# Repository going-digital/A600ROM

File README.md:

# A600ROM
Flash ROM Kickstart replacement for the Amiga A600

## This project is in development and currently untested.

This project replaces the Kickstart ROM in the Amiga A600 with a 2M x 16 Flash chip. This allows 4 x 512kB or 2 x 1MB Flash banks.

Initial programming of the first Kickstart must be done with a programmer. But after that, programming can be done in-circuit from the Amiga.

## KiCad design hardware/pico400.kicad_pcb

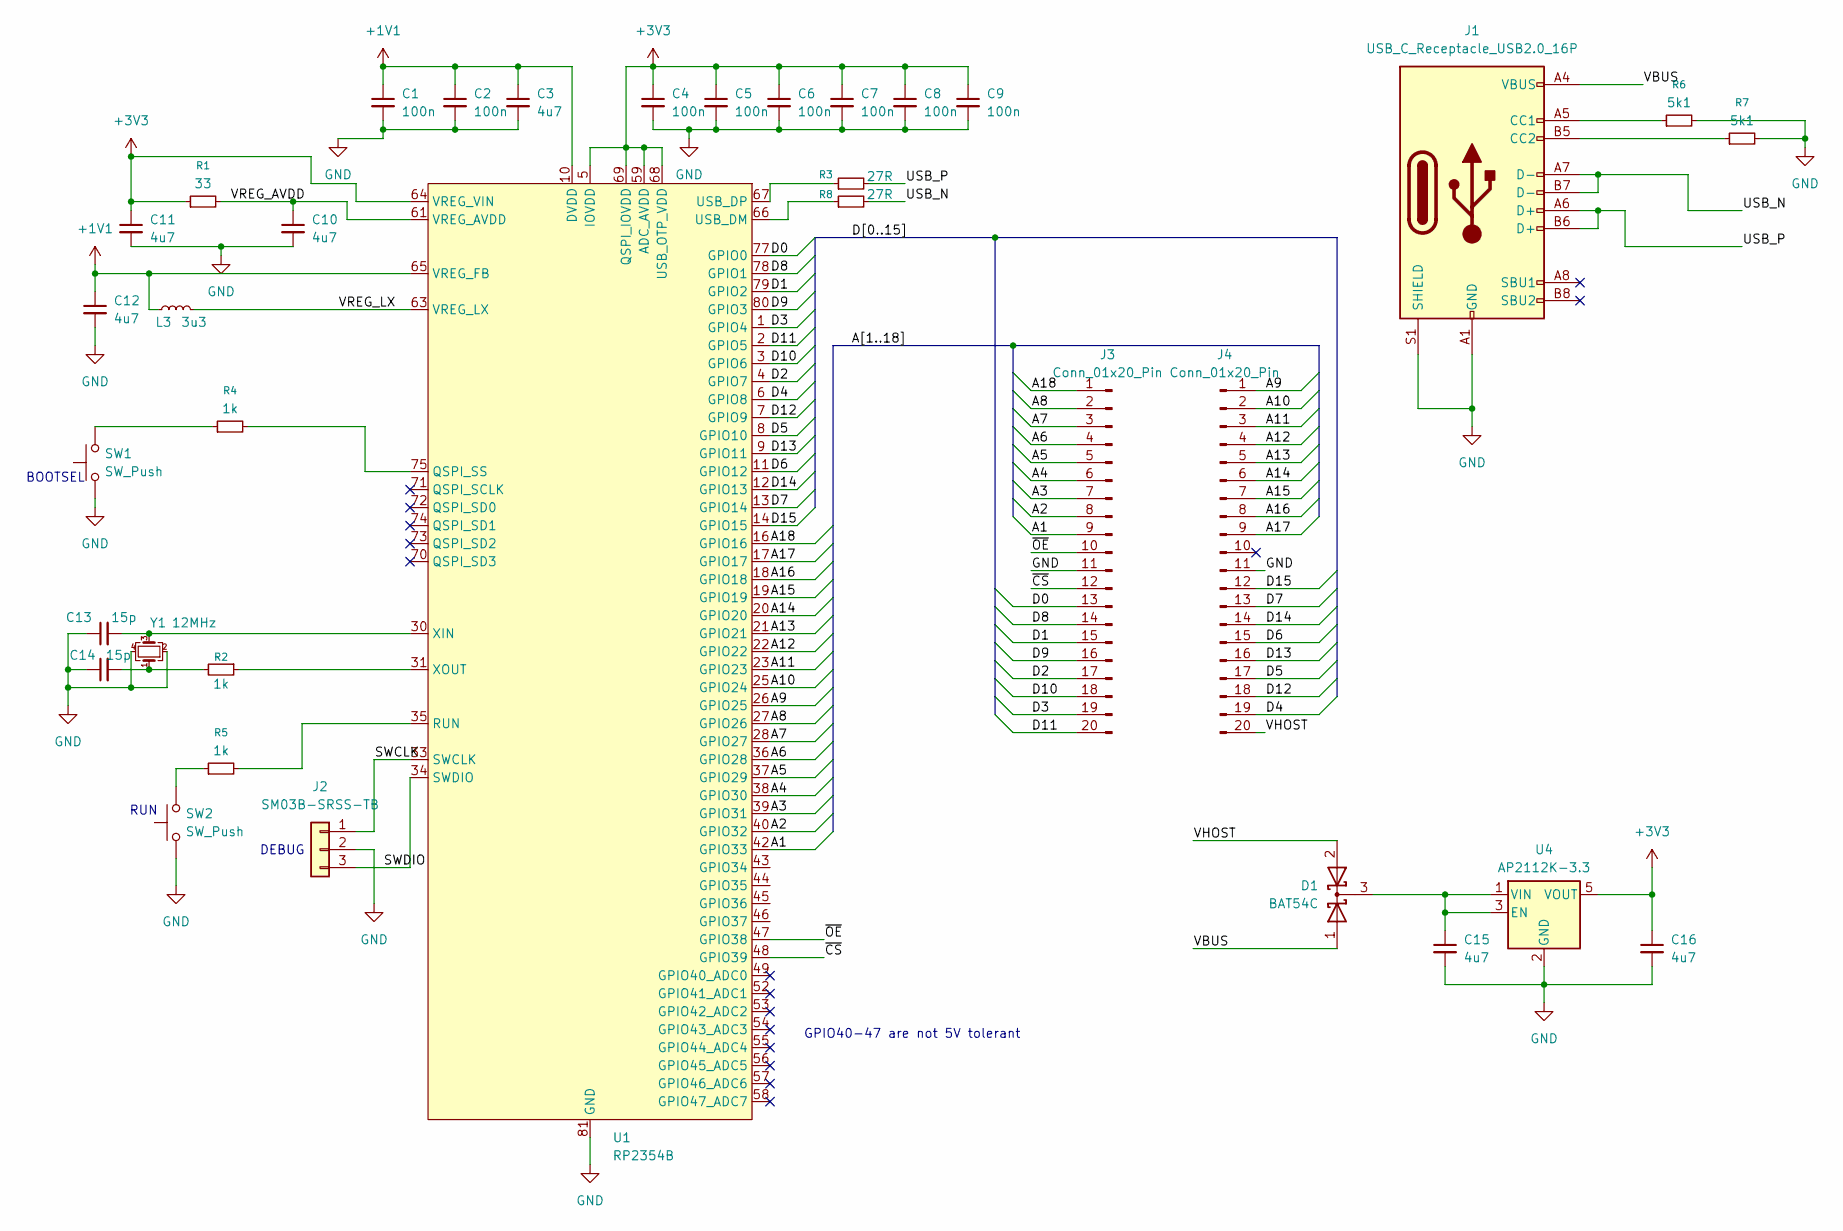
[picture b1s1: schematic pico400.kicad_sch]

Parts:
C1, C2, C4, C5, C6, C7, C8, C9: 100n; C_0402_1005Metric
C3, C10, C11, C12, C15, C16: 4u7; C_0402_1005Metric
C13, C14: 15p; C_0402_1005Metric
D1: BAT54C; SOT-23
J1: USB_C_Receptacle_USB2.0_16P; USB_C_Receptacle_HCTL_HC-TYPE-C-16P-01A; JLCPCB Part # C2765186
J2: SM03B-SRSS-TB; JST_SH_SM03B-SRSS-TB_1x03-1MP_P1.00mm_Horizontal
J3, J4: Conn_01x20_Pin; PinHeader_1x20_P2.54mm_Vertical
L3: 3u3; L_0805_2012Metric
R1: 33; R_0402_1005Metric
R2, R4, R5: 1k; R_0402_1005Metric
R3, R8: 27R; R_0402_1005Metric
R6, R7: 5k1; R_0402_1005Metric
SW1, SW2: SW_Push; SW_Tactile_SPST_NO_Straight_CK_PTS636Sx25SMTRLFS
U1: RP2354B; QFN-80-1EP_10x10mm_P0.4mm_EP3.4x3.4mm_ThermalVias; JLCPCB Part # C39843328
U4: AP2112K-3.3; SOT-23-5
Y1: 12MHz; Crystal_SMD_0603-4Pin_6.0x3.5mm

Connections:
+1V1: C1.1, C2.1, C3.1, C12.1, L3.1, U1.10 (DVDD), U1.32 (DVDD), U1.51 (DVDD), U1.65 (VREG_FB)
+3V3: C4.1, C5.1, C6.1, C7.1, C8.1, C9.1, C11.1, C16.1, R1.1, U1.5 (IOVDD), U1.15 (IOVDD), U1.24 (IOVDD), U1.29 (IOVDD), U1.41 (IOVDD), U1.50 (IOVDD), U1.59 (ADC_AVDD), U1.60 (IOVDD), U1.64 (VREG_VIN), U1.68 (USB_OTP_VDD), U1.69 (QSPI_IOVDD), U1.76 (IOVDD), U4.5 (VOUT)
/A1: J3.9, U1.42 (GPIO33)
/A2: J3.8, U1.40 (GPIO32)
/A3: J3.7, U1.39 (GPIO31)
/A4: J3.6, U1.38 (GPIO30)
/A5: J3.5, U1.37 (GPIO29)
/A6: J3.4, U1.36 (GPIO28)
/A7: J3.3, U1.28 (GPIO27)
/A8: J3.2, U1.27 (GPIO26)
/A9: J4.1, U1.26 (GPIO25)
/A10: J4.2, U1.25 (GPIO24)
/A11: J4.3, U1.23 (GPIO23)
/A12: J4.4, U1.22 (GPIO22)
/A13: J4.5, U1.21 (GPIO21)
/A14: J4.6, U1.20 (GPIO20)
/A15: J4.7, U1.19 (GPIO19)
/A16: J4.8, U1.18 (GPIO18)
/A17: J4.9, U1.17 (GPIO17)
/A18: J3.1, U1.16 (GPIO16)
/D0: J3.13, U1.77 (GPIO0)
/D1: J3.15, U1.79 (GPIO2)
/D2: J3.17, U1.4 (GPIO7)
/D3: J3.19, U1.1 (GPIO4)
/D4: J4.19, U1.6 (GPIO8)
/D5: J4.17, U1.8 (GPIO10)
/D6: J4.15, U1.11 (GPIO12)
/D7: J4.13, U1.13 (GPIO14)
/D8: J3.14, U1.78 (GPIO1)
/D9: J3.16, U1.80 (GPIO3)
/D10: J3.18, U1.3 (GPIO6)
/D11: J3.20, U1.2 (GPIO5)
/D12: J4.18, U1.7 (GPIO9)
/D13: J4.16, U1.9 (GPIO11)
/D14: J4.14, U1.12 (GPIO13)
/D15: J4.12, U1.14 (GPIO15)
/SWCLK: J2.1, U1.33 (SWCLK)
/SWDIO: J2.3, U1.34 (SWDIO)
/USB_N: J1.A7 (D-), J1.B7 (D-), R8.2
/USB_P: J1.A6 (D+), J1.B6 (D+), R3.2
/VBUS: D1.1 (A), J1.A4 (VBUS), J1.A9 (VBUS), J1.B4 (VBUS), J1.B9 (VBUS)
/VHOST: D1.2 (A), J4.20
/VREG_AVDD: C10.1, R1.2, U1.61 (VREG_AVDD)
/VREG_LX: L3.2, U1.63 (VREG_LX)
/~CS: J3.12, U1.48 (GPIO39)
/~OE: J3.10, U1.47 (GPIO38)
GND: C1.2, C2.2, C3.2, C4.2, C5.2, C6.2, C7.2, C8.2, C9.2, C10.2, C11.2, C12.2, C13.1, C14.1, C15.2, C16.2, J1.A1 (GND), J1.A12 (GND), J1.B1 (GND), J1.B12 (GND), J1.S1 (SHIELD), J2.2, J3.11, J4.11, R6.2, R7.2, SW1.1, SW2.1, U1.62 (VREG_PGND), U1.81 (GND), U4.2 (GND), Y1.2, Y1.4
unnamed: C14.2, R2.2, Y1.1
unnamed: C15.1, D1.3 (K), U4.1 (VIN), U4.3 (EN)
unnamed: J1.A5 (CC1), R6.1
unnamed: J1.B5 (CC2), R7.1
unnamed: R4.1, SW1.2
unnamed: R5.1, SW2.2
unnamed: R4.2, U1.75 (QSPI_SS)
unnamed: R5.2, U1.35 (RUN)
unnamed: R8.1, U1.66 (USB_DM)
unnamed: R3.1, U1.67 (USB_DP)
unnamed: C13.2, U1.30 (XIN), Y1.3
unnamed: R2.1, U1.31 (XOUT)

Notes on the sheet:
BOOTSEL
RUN
DEBUG
GPIO40-47 are not 5V tolerant

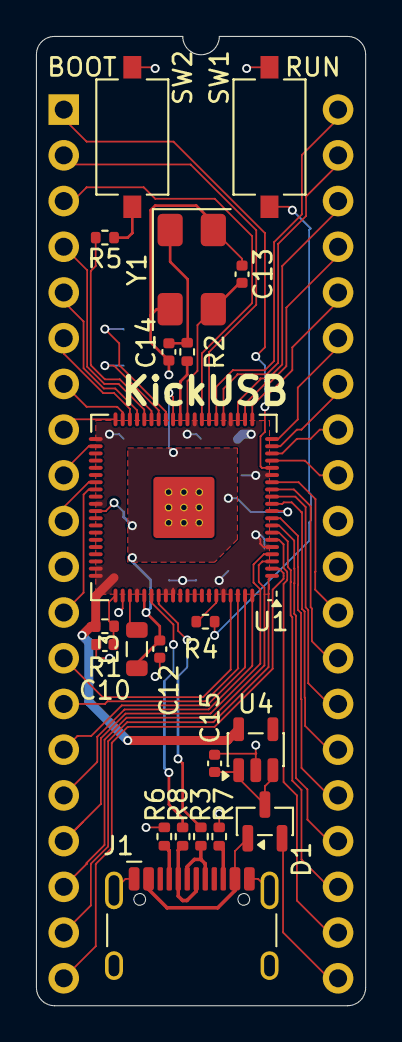
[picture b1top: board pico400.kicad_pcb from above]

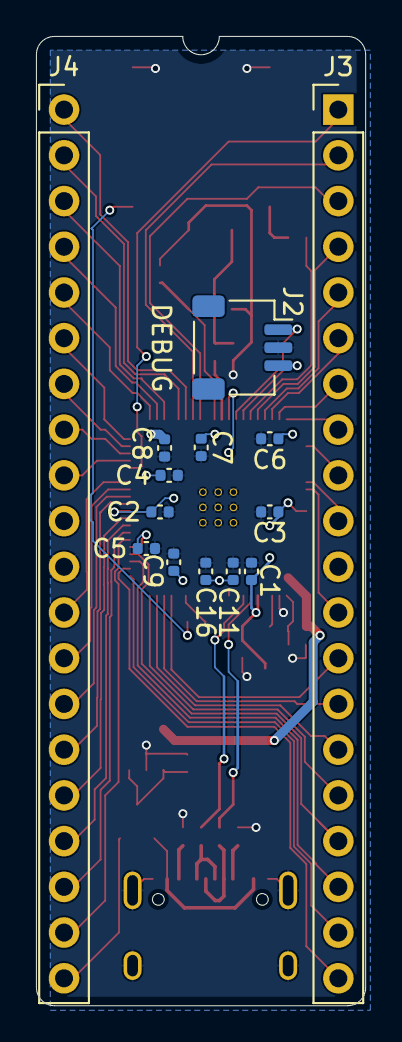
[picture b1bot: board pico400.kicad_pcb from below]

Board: 2 copper layers, 18.3 x 53.8 mm, 35 parts (14 on the bottom side), 59 nets.

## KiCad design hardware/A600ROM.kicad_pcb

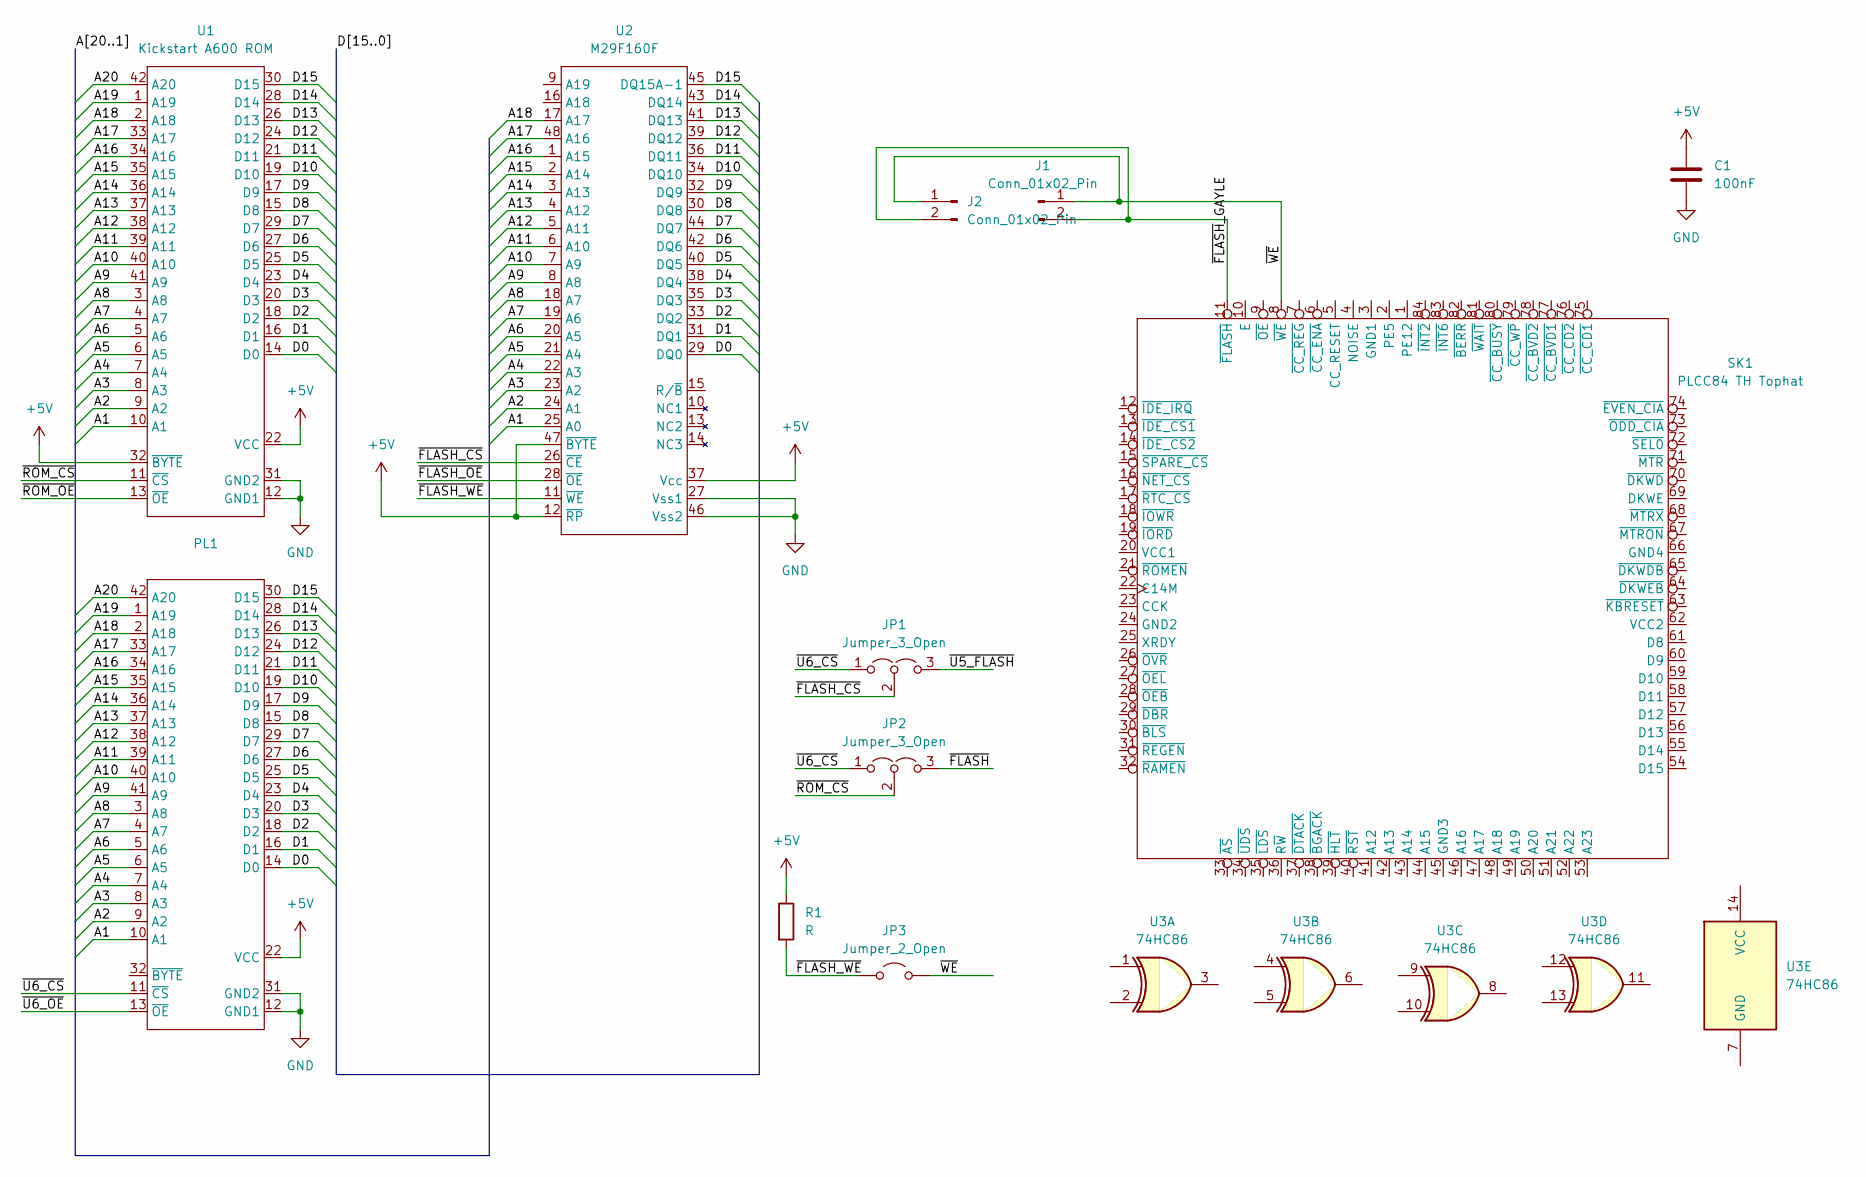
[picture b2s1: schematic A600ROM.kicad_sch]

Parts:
C1: 100nF; C_0603_1608Metric_Pad1.08x0.95mm_HandSolder
J1, J2: Conn_01x02_Pin; PinHeader_1x02_P2.54mm_Vertical
JP1, JP2: Jumper_3_Open; PinHeader_1x03_P2.54mm_Vertical
JP3: Jumper_2_Open; PinHeader_1x02_P2.54mm_Vertical
PL1: DIP-42_W15.24mm_SMDHeader_SmallPads
R1: R; R_0805_2012Metric_Pad1.20x1.40mm_HandSolder
SK1: PLCC84 TH Tophat; PLCC-84_THT-Socket-Tophat
U1: Kickstart A600 ROM; DIP-42_W15.24mm_SMDSocket_SmallPads
U2: M29F160F; TSOP-I-48_18.4x12mm_P0.5mm
U3: 74HC86

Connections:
+5V: C1.1, PL1.22 (VCC), R1.1, U1.22 (VCC), U1.32 (~BYTE), U2.12 (~RP), U2.37 (Vcc), U2.47 (~BYTE)
/A1: PL1.10 (A1), U1.10 (A1), U2.25 (A0)
/A2: PL1.9 (A2), U1.9 (A2), U2.24 (A1)
/A3: PL1.8 (A3), U1.8 (A3), U2.23 (A2)
/A4: PL1.7 (A4), U1.7 (A4), U2.22 (A3)
/A5: PL1.6 (A5), U1.6 (A5), U2.21 (A4)
/A6: PL1.5 (A6), U1.5 (A6), U2.20 (A5)
/A7: PL1.4 (A7), U1.4 (A7), U2.19 (A6)
/A8: PL1.3 (A8), U1.3 (A8), U2.18 (A7)
/A9: PL1.41 (A9), U1.41 (A9), U2.8 (A8)
/A10: PL1.40 (A10), U1.40 (A10), U2.7 (A9)
/A11: PL1.39 (A11), U1.39 (A11), U2.6 (A10)
/A12: PL1.38 (A12), U1.38 (A12), U2.5 (A11)
/A13: PL1.37 (A13), U1.37 (A13), U2.4 (A12)
/A14: PL1.36 (A14), U1.36 (A14), U2.3 (A13)
/A15: PL1.35 (A15), U1.35 (A15), U2.2 (A14)
/A16: PL1.34 (A16), U1.34 (A16), U2.1 (A15)
/A17: PL1.33 (A17), U1.33 (A17), U2.48 (A16)
/A18: PL1.2 (A18), U1.2 (A18), U2.17 (A17)
/A19: PL1.1 (A19), U1.1 (A19), U2.16 (A18)
/A20: PL1.42 (A20), U1.42 (A20), U2.9 (A19)
/D0: PL1.14 (D0), U1.14 (D0), U2.29 (DQ0)
/D1: PL1.16 (D1), U1.16 (D1), U2.31 (DQ1)
/D2: PL1.18 (D2), U1.18 (D2), U2.33 (DQ2)
/D3: PL1.20 (D3), U1.20 (D3), U2.35 (DQ3)
/D4: PL1.23 (D4), U1.23 (D4), U2.38 (DQ4)
/D5: PL1.25 (D5), U1.25 (D5), U2.40 (DQ5)
/D6: PL1.27 (D6), U1.27 (D6), U2.42 (DQ6)
/D7: PL1.29 (D7), U1.29 (D7), U2.44 (DQ7)
/D8: PL1.15 (D8), U1.15 (D8), U2.30 (DQ8)
/D9: PL1.17 (D9), U1.17 (D9), U2.32 (DQ9)
/D10: PL1.19 (D10), U1.19 (D10), U2.34 (DQ10)
/D11: PL1.21 (D11), U1.21 (D11), U2.36 (DQ11)
/D12: PL1.24 (D12), U1.24 (D12), U2.39 (DQ12)
/D13: PL1.26 (D13), U1.26 (D13), U2.41 (DQ13)
/D14: PL1.28 (D14), U1.28 (D14), U2.43 (DQ14)
/D15: PL1.30 (D15), U1.30 (D15), U2.45 (DQ15A-1)
/~FLASH_CS: JP1.2 (C), U2.26 (~CE)
/~FLASH_OE: U2.28 (~OE)
/~FLASH_WE: JP3.1 (A), R1.2, U2.11 (~WE)
/~FLASH: JP2.3 (B)
/~FLASH_GAYLE: J1.2, J2.2, SK1.11 (~FLASH)
/~ROM_CS: JP2.2 (C), U1.11 (~CS)
/~ROM_OE: U1.13 (~OE)
/~U5_FLASH: JP1.3 (B)
/~U6_CS: JP1.1 (A), JP2.1 (A), PL1.11 (~CS)
/~U6_OE: PL1.13 (~OE)
/~WE: J1.1, J2.1, JP3.2 (B), SK1.8 (~WE)
GND: C1.2, PL1.12 (GND1), PL1.31 (GND2), U1.12 (GND1), U1.31 (GND2), U2.27 (Vss1), U2.46 (Vss2)

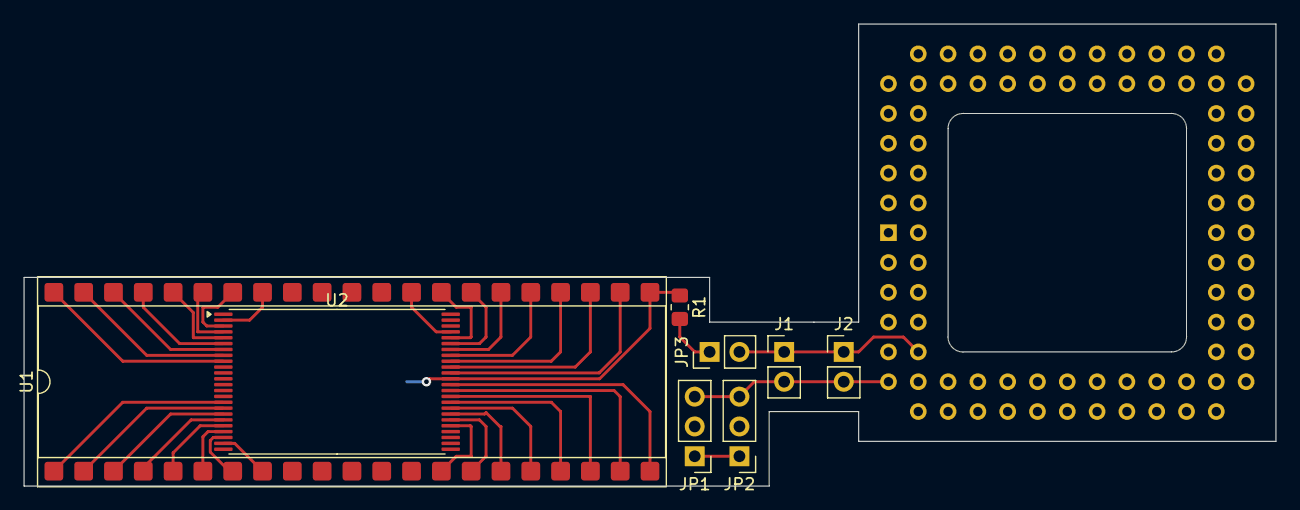
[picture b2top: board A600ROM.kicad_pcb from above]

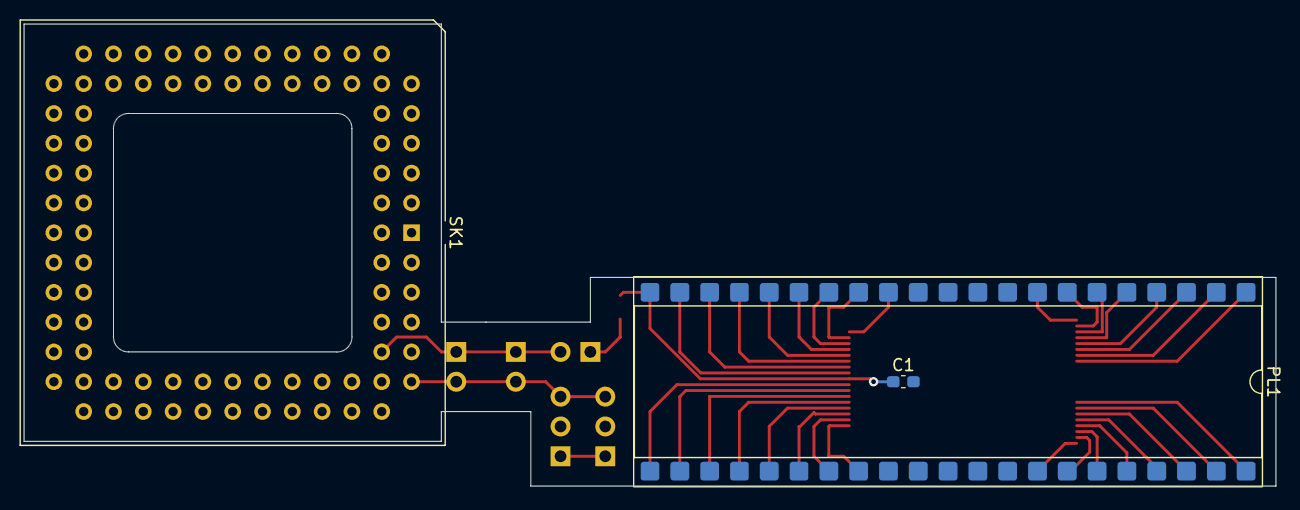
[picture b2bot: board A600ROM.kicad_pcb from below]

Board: 4 copper layers, 106.7 x 39.4 mm, 11 parts (3 on the bottom side), 44 nets.

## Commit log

2025-08-03 Gayle hat
    Add hat. Partially unrouted.
2025-08-04 Add connectors
2025-12-17 Progress
